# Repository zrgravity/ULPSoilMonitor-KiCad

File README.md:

# ULPSoilMonitor-KiCad

- Originally created by https://github.com/DerFlob
- See https://blog.m3k.cc/2021/01/ultra-low-power-soil-monitor/
- Original Git Repo: https://cgit.derflob.de/KiCad/ULPSoilMonitor.git
- Arduino source: https://github.com/zrgravity/ULPSoilMonitor-Arduino

Low Power Soil moisture monitor using off-the-shelf moisture sensors and ESP32. OSHW designed in KiCad and software in Arduino.

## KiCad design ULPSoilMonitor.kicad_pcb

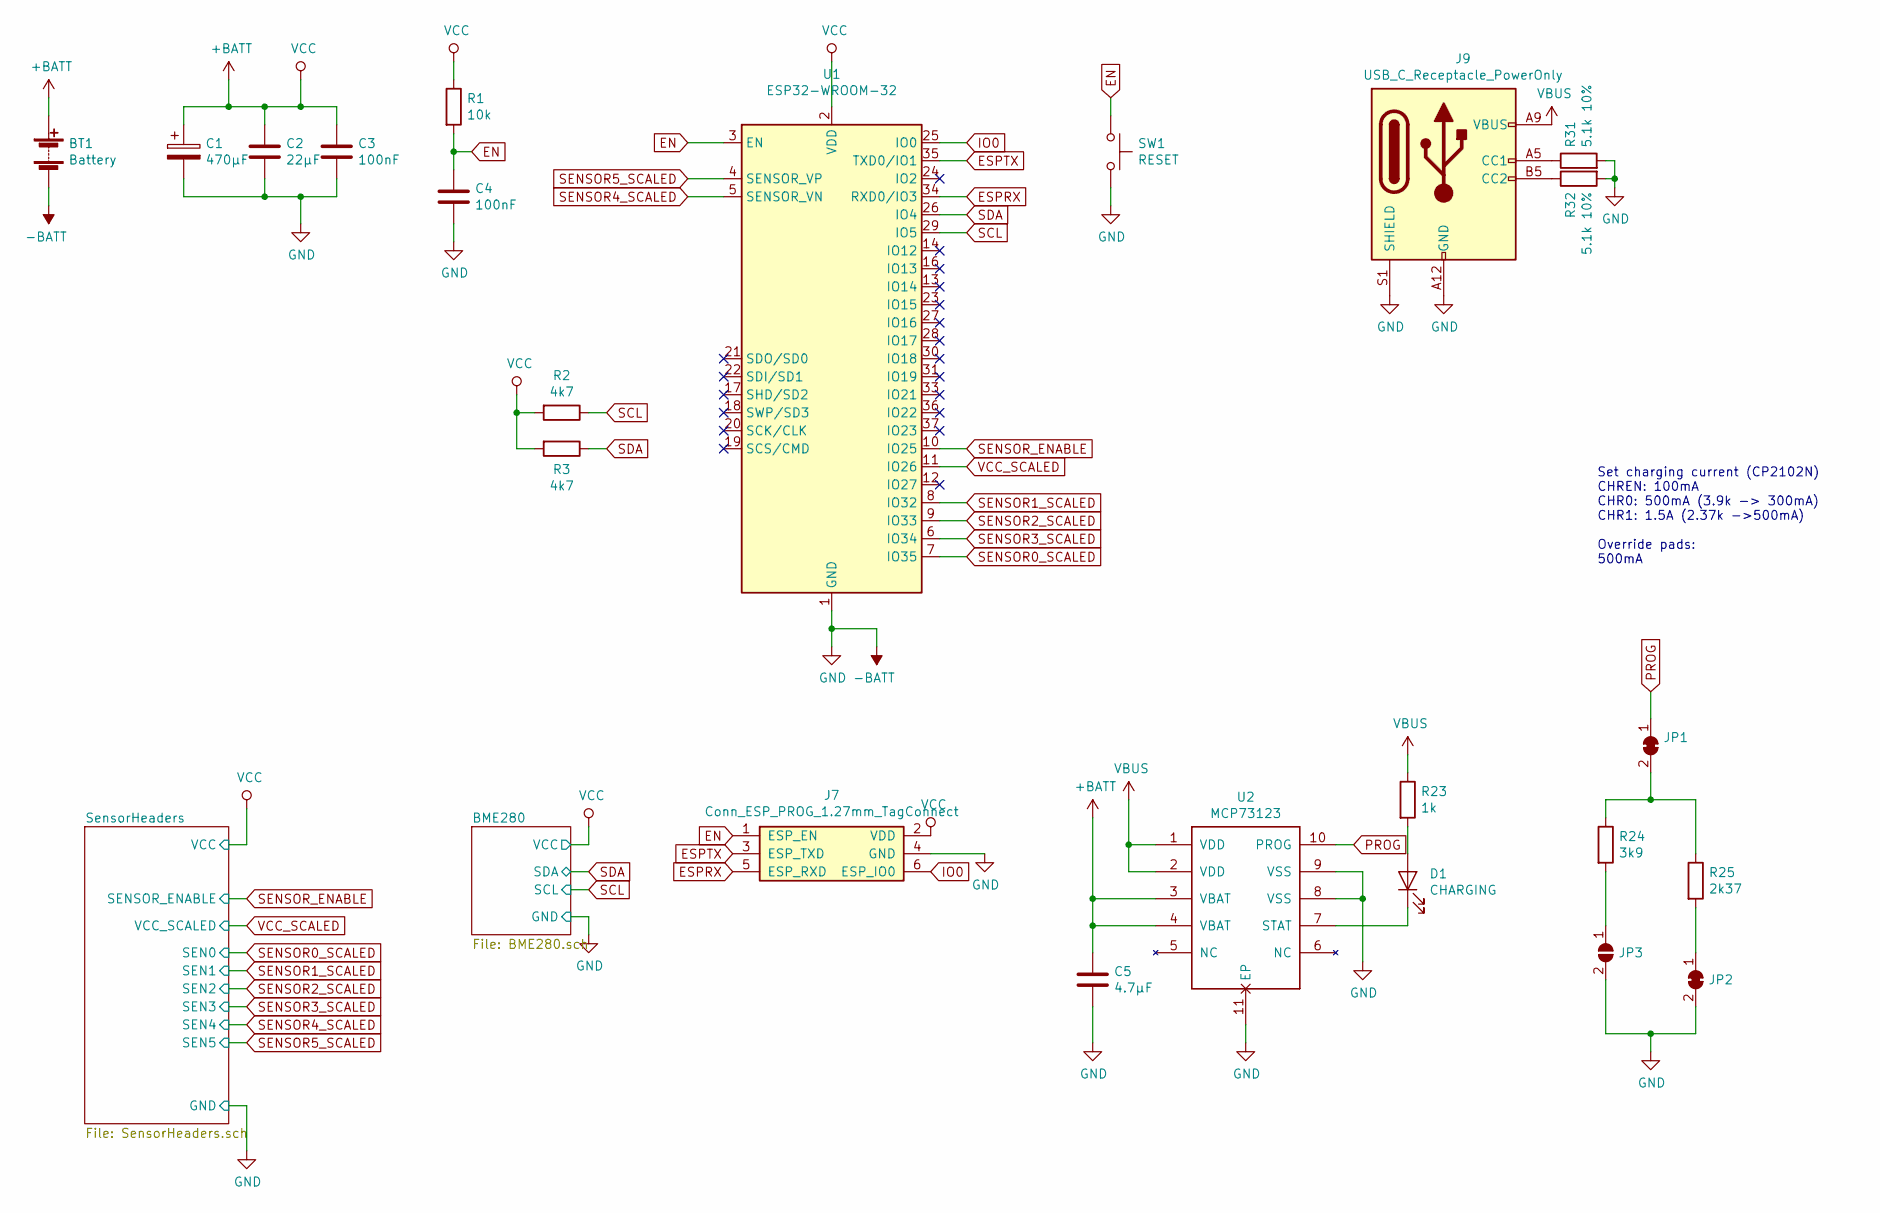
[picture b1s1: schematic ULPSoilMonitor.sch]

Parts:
BT1: Battery; BatteryHolder_BHC-18650-1P-2P
C1: 470μF; CP_Elec_6.3x7.7; LCSC C335982
C2: 22μF; C_0805_2012Metric; LCSC C45783
C3, C4: 100nF; C_0805_2012Metric; LCSC C49678
C5: 4.7μF; C_0805_2012Metric; LCSC C1779
D1: CHARGING; LED_0805_2012Metric; LCSC C84256
J7: Conn_ESP_PROG_1.27mm_TagConnect; Tag-Connect_TC2030-IDC-NL_2x03_P1.27mm_Vertical
J9: USB_C_Receptacle_PowerOnly; TYPE-C-31-M-17.kicad_mod
JP1: Charg_enable; SolderJumper-2_P1.3mm_Bridged_RoundedPad1.0x1.5mm
JP2: Charge_500mA; SolderJumper-2_P1.3mm_Bridged_RoundedPad1.0x1.5mm
JP3: Charge_300mA; SolderJumper-2_P1.3mm_Open_RoundedPad1.0x1.5mm
R1: 10k; R_0805_2012Metric; LCSC C17414
R2, R3: 4k7; R_0805_2012Metric; LCSC C17673
R23: 1k; R_0805_2012Metric; LCSC C17513
R24: 3k9; R_0805_2012Metric; LCSC C17614
R25: 2k37; R_0805_2012Metric; LCSC C17523
R31, R32: 5.1k 10%; R_0805_2012Metric; LCSC C17513
SW1: RESET; SW_SPST_FSMSM; LCSC C354943
U1: ESP32-WROOM-32; LCSC C473012
U2: MCP73123; DFN-10-1EP_3x3mm_P0.5mm_EP1.65x2.38mm

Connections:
+BATT: BT1.1 (+), C1.1, C2.1, C3.1, C5.1, J7.2 (VDD), R1.1, R2.2, R3.2, U1.2 (VDD), U2.3 (VBAT), U2.4 (VBAT); also elsewhere on the board
-BATT: BT1.2 (-), C1.2, C2.2, C3.2, C4.2, C5.2, J7.4 (GND), J9.A12 (GND), J9.B12 (GND), J9.S1 (SHIELD), JP2.2 (B), JP3.2 (B), R31.2, R32.2, SW1.2, U1.1 (GND), U1.15 (GND), U1.38 (GND), U1.39 (GND), U2.8 (VSS), U2.9 (VSS), U2.11 (EP); also elsewhere on the board
EN: C4.1, J7.1 (ESP_EN), R1.2, SW1.1, U1.3 (EN)
ESPRX: J7.5 (ESP_RXD), U1.34 (RXD0/IO3)
ESPTX: J7.3 (ESP_TXD), U1.35 (TXD0/IO1)
IO0: J7.6 (ESP_IO0), U1.25 (IO0)
unnamed: D1.1 (K), U2.7 (STAT)
unnamed: D1.2 (A), R23.2
unnamed: J9.A5 (CC1), R31.1
unnamed: J9.B5 (CC2), R32.1
unnamed: JP1.2 (B), R24.1, R25.1
unnamed: JP2.1 (A), R25.2
unnamed: JP3.1 (A), R24.2
PROG: JP1.1 (A), U2.10 (PROG)
SCL: R2.1, U1.29 (IO5); also elsewhere on the board
SDA: R3.1, U1.26 (IO4); also elsewhere on the board
SENSOR0_SCALED: U1.7 (IO35); also elsewhere on the board
SENSOR1_SCALED: U1.8 (IO32); also elsewhere on the board
SENSOR2_SCALED: U1.9 (IO33); also elsewhere on the board
SENSOR3_SCALED: U1.6 (IO34); also elsewhere on the board
SENSOR4_SCALED: U1.5 (SENSOR_VN); also elsewhere on the board
SENSOR5_SCALED: U1.4 (SENSOR_VP); also elsewhere on the board
SENSOR_ENABLE: U1.10 (IO25); also elsewhere on the board
VBUS: J9.A9 (VBUS), J9.B9 (VBUS), R23.1, U2.1 (VDD), U2.2 (VDD)
VCC_SCALED: U1.11 (IO26); also elsewhere on the board

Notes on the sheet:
Set charging current (CP2102N) CHREN: 100mA CHR0: 500mA (3.9k -> 300mA) CHR1: 1.5A (2.37k ->500mA) Override pads: 500mA

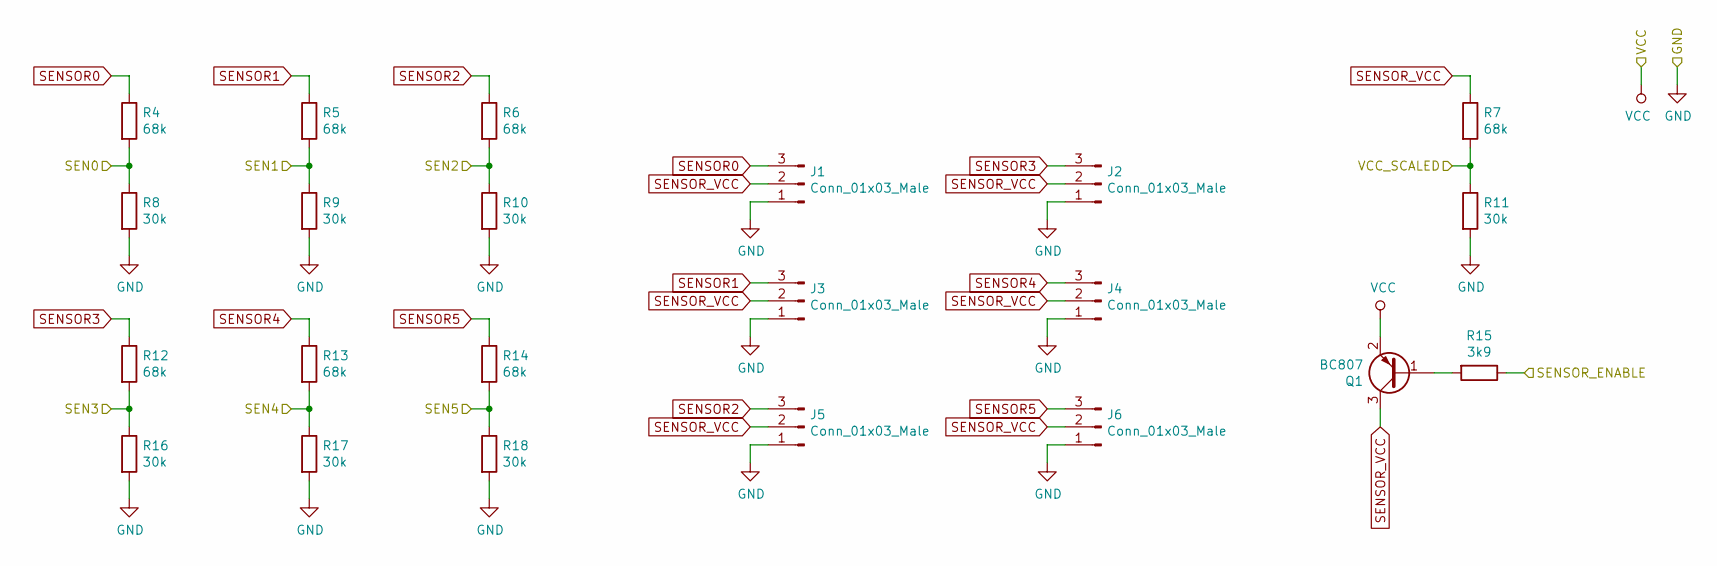
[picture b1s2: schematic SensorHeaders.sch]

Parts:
J1, J2, J3, J4, J5, J6: Conn_01x03_Male; PinHeader_1x03_P2.54mm_Vertical
Q1: BC807; SOT-23; LCSC C8587
R4, R5, R6, R7, R12, R13, R14: 68k; R_0805_2012Metric; LCSC C17801
R8, R9, R10, R11, R16, R17, R18: 30k; R_0805_2012Metric; LCSC C17621
R15: 3k9; R_0805_2012Metric; LCSC C17614

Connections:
+BATT: Q1.2 (E); also elsewhere on the board
-BATT: J1.1, J2.1, J3.1, J4.1, J5.1, J6.1, R8.2, R9.2, R10.2, R11.2, R16.2, R17.2, R18.2; also elsewhere on the board
unnamed: Q1.1 (B), R15.2
SENSOR0: J1.3, R4.1
SENSOR0_SCALED: R4.2, R8.1; also elsewhere on the board
SENSOR1: J3.3, R5.1
SENSOR1_SCALED: R5.2, R9.1; also elsewhere on the board
SENSOR2: J5.3, R6.1
SENSOR2_SCALED: R6.2, R10.1; also elsewhere on the board
SENSOR3: J2.3, R12.1
SENSOR3_SCALED: R12.2, R16.1; also elsewhere on the board
SENSOR4: J4.3, R13.1
SENSOR4_SCALED: R13.2, R17.1; also elsewhere on the board
SENSOR5: J6.3, R14.1
SENSOR5_SCALED: R14.2, R18.1; also elsewhere on the board
SENSOR_ENABLE: R15.1; also elsewhere on the board
SENSOR_VCC: J1.2, J2.2, J3.2, J4.2, J5.2, J6.2, Q1.3 (C), R7.1
VCC_SCALED: R7.2, R11.1; also elsewhere on the board

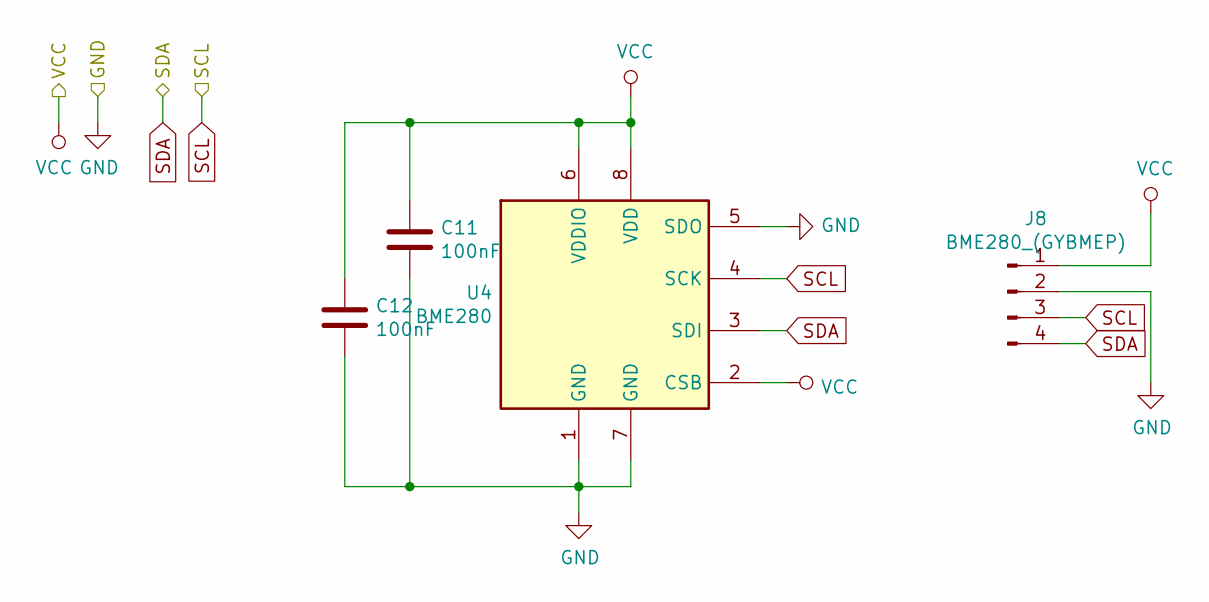
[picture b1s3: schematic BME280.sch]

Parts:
C11, C12: 100nF; C_0805_2012Metric; LCSC C49678
J8: BME280_(GYBMEP); PinHeader_1x04_P2.54mm_Vertical
U4: BME280; Bosch_LGA-8_2.5x2.5mm_P0.65mm_ClockwisePinNumbering

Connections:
+BATT: C11.1, C12.1, J8.1, U4.2 (CSB), U4.6 (VDDIO), U4.8 (VDD); also elsewhere on the board
-BATT: C11.2, C12.2, J8.2, U4.1 (GND), U4.5 (SDO), U4.7 (GND); also elsewhere on the board
SCL: J8.3, U4.4 (SCK); also elsewhere on the board
SDA: J8.4, U4.3 (SDI); also elsewhere on the board

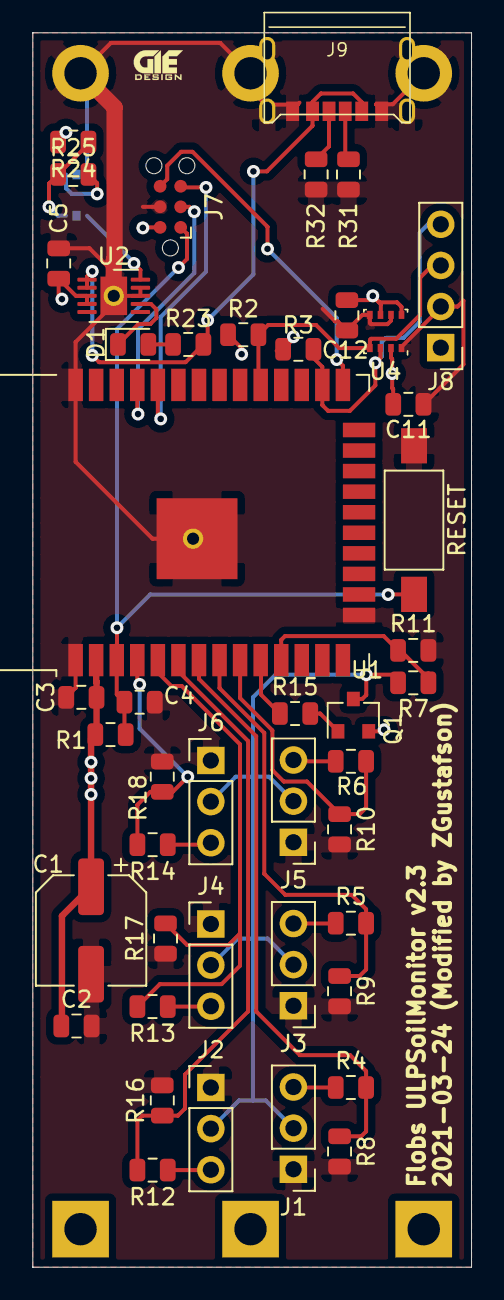
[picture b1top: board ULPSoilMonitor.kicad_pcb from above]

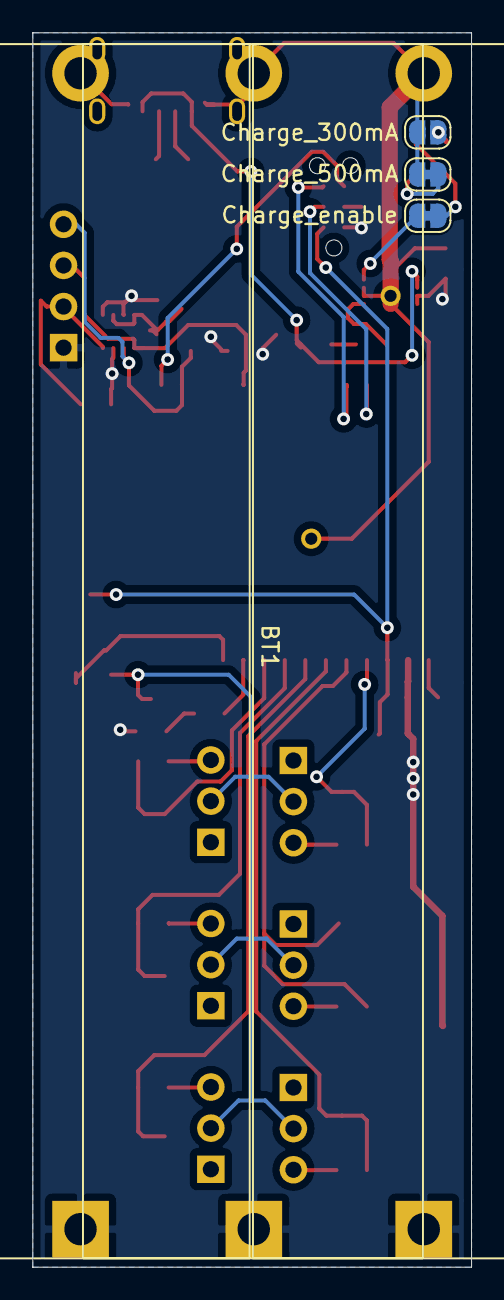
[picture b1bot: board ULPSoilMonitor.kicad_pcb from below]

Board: 2 copper layers, 27.1 x 76.2 mm, 49 parts (4 on the bottom side), 33 nets.

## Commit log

2020-04-26 ESP32-based soil moisture sensor
2020-05-06 fix cap unit of measure
2020-05-16 update to use 18650 LiFePO4 cells
    * connectors for one or two 18650 cells
    * jumper to switch between battery & USB power
    * add optional BME380
    * reset push button
    * more caps
2020-06-13 add additional spacing between sensor connectors
2020-06-14 move USB connector further over the edge
2020-06-23 change USB to Serial chip, support charging
    * exchanges FTDI FT231X for SILabs CP2102N
    * adds MicroChip MCP73123 for LiFePO4 charging
2020-06-26 update drawing to 882a528a10f6fb48f6454efd446c1280f51ad1f8
2020-07-05 route around vias for soldering
2020-07-05 minor layout adjustments
2020-07-05 remove unused text
2020-07-05 update version
2021-01-27 Add JCLPCB/LCSC part numbers
2021-01-27 Add gerber and assembly files for original design
2021-03-24 Set USB-serial DNP
    Disable USB-serial
    Add switches for LiFePo charger PROG setting
2021-03-24 Update jumper names
2021-03-24 Layout jumpers on PCB
2021-03-24 Add .gitignore for KiCad
2021-03-24 Add USB-C connector
2021-03-24 DNP micro-usb
2021-03-24 Set charge current to 500mA
2021-03-24 Remove USB-mini connector
2021-03-24 Remove USB-serial converter
2021-03-24 Add Tag-Connect for programming
2021-03-24 Fix ERC component errors
2021-03-24 Layout
2021-03-24 Edit silkscreen
